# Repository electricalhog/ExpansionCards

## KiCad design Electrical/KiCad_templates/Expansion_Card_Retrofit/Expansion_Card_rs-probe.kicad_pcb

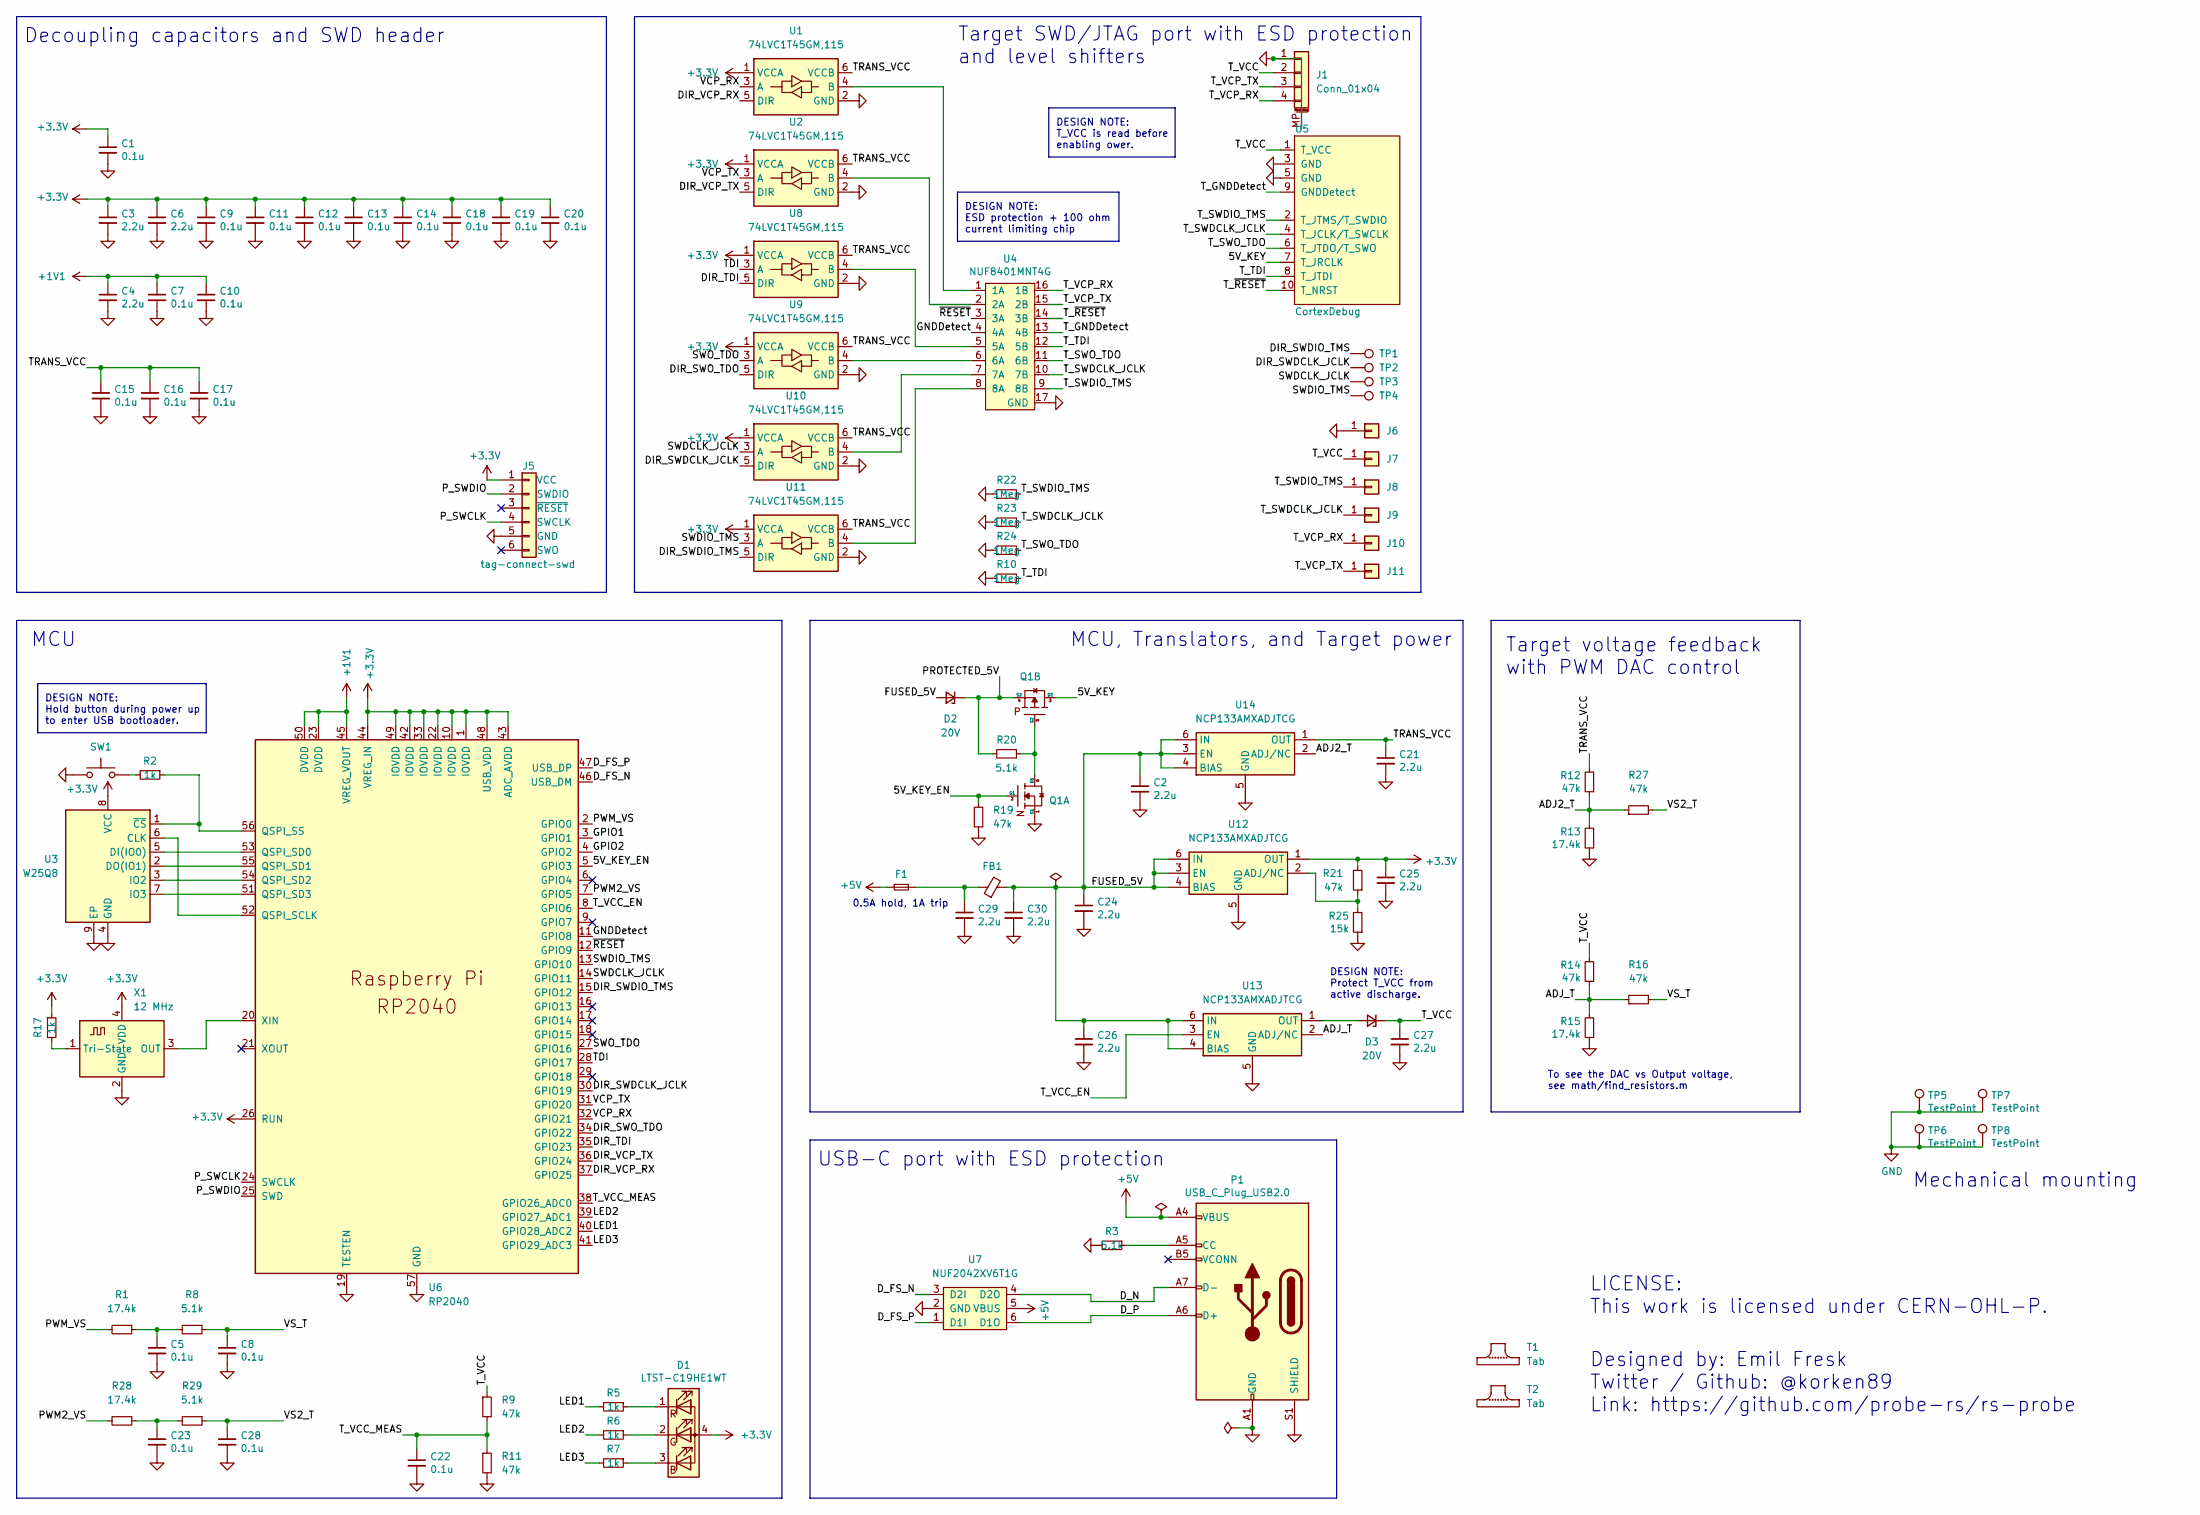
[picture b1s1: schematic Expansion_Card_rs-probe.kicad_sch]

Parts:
C1, C5, C7, C8, C9, C10, C11, C12, C13, C14, C15, C16, C17, C18, C19, C20, C22, C23, C28: 0.1u; C_0402; Tolerance 25V, X7R; LCSC C56392
C2, C3, C4, C6, C21, C24, C25, C26, C27, C29, C30: 2.2u; C_0402; Tolerance 10V, X5R; LCSC C77002
D1: LTST-C19HE1WT; LED_LiteOn_LTST-C19HE1WT; LCSC C427425, C458749
D2, D3: 20V; D_0402_1005Metric
F1: Fuse_Small; Fuse_0603_1608Metric; LCSC C210357
FB1: BLM15AX601SN1D; R_0402
J1: Conn_01x04; PinHeader_1x04_P1.00mm_Vertical_SMD_Pin1Left
J5: tag-connect-swd; Tag-Connect_TC2030-IDC-NL_2x03_P1.27mm_Vertical
J6, J7, J8, J9, J10, J11: Conn_01x01; pad_1.5x2.0mm
P1: USB_C_Plug_USB2.0; USB_C_Plug_Molex_105444
Q1: NTZD3155C or CMLDM3757-TR-PBFREE or DMC2400UV-7 o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; SOT-563; LCSC C895156, C236117, C3280275, C177025, C2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
R1, R13, R15, R28: 17.4k; R_0402; Tolerance 1%; LCSC C409673
R2, R5, R6, R7, R17: 1k; R_0402; Tolerance 1%; LCSC C106235
R3, R8, R29: 5.1k; R_0402; Tolerance 1%; LCSC C105872
R9, R11, R12, R14, R16, R19, R21, R27: 47k; R_0402; Tolerance 1%; LCSC C144757
R10, R22, R23, R24: 1Meg; R_0402; Tolerance 1%; LCSC C138033
R20: 5.1k; R_0402; Tolerance 1%
R25: 15k; R_0402; Tolerance 1%; LCSC C409673
SW1: B3U-1000P; SW_SPST_B3U-1000P; LCSC C79148, C713481
T1, T2: Tab
TP1, TP2, TP3, TP4: TestPoint; TestPoint_Pad_D1.0mm
TP5, TP6, TP7, TP8: TestPoint; TestPoint_Pad_1.5x1.5mm
U1, U2, U8, U9, U10, U11: 74LVC1T45GM,115; SOT-886; LCSC C548481, C548480, C548479
U3: W25Q8; USON-8-3x2mm-EP; LCSC C2063555, C2759920, C2983691, C559220, 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
U4: NUF8401MNT4G; DFN-16-1EP_1.6x4mm_P0.5mm; LCSC C895158
U5: CortexDebug; SHF-105-01-PCBEdge; LCSC C2935458, C150517, C920815
U6: RP2040; RP2040-QFN-56; LCSC C2040
U7: NUF2042XV6T1G; SOT-563; LCSC C90707
U12, U13, U14: NCP133AMXADJTCG; DFN-6-1EP_1.2x1.2mm_P0.4mm_EP0.3x0.94mm_PullBack; LCSC C457672
X1: 12 MHz; Crystal_SMD_2520-4Pin_2.5x2.0mm; LCSC C255991, C2681259, C3034288, C2901596

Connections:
+1V1: C4.1, C7.1, C10.1, U6.23 (DVDD), U6.45 (VREG_VOUT), U6.50 (DVDD)
+3.3V: C1.1, C3.1, C6.1, C9.1, C11.1, C12.1, C13.1, C14.1, C18.1, C19.1, C20.1, C25.1, D1.4 (A), J5.1 (VCC), R17.1, R21.2, U1.1 (VCCA), U2.1 (VCCA), U3.8 (VCC), U6.1 (IOVDD), U6.10 (IOVDD), U6.22 (IOVDD), U6.26 (RUN), U6.33 (IOVDD), U6.42 (IOVDD), U6.43 (ADC_AVDD), U6.44 (VREG_IN), U6.48 (USB_VDD), U6.49 (IOVDD), U8.1 (VCCA), U9.1 (VCCA), U10.1 (VCCA), U11.1 (VCCA), U12.1 (OUT), X1.4 (VDD)
+5V: F1.1, P1.A4 (VBUS), P1.A9 (VBUS), P1.B4 (VBUS), P1.B9 (VBUS), U7.5 (VBUS)
/5V_KEY: Q1.3 (D2), U5.7 (T_JRCLK)
/5V_KEY_EN: Q1.2 (G1), R19.2, U6.5 (GPIO3)
/ADJ2_T: R12.1, R13.2, R27.1, U14.2 (ADJ/NC)
/ADJ_T: R14.1, R15.2, R16.1, U13.2 (ADJ/NC)
/DIR_SWDCLK_JCLK: TP2.1, U6.30 (GPIO19), U10.5 (DIR)
/DIR_SWDIO_TMS: TP1.1, U6.15 (GPIO12), U11.5 (DIR)
/DIR_SWO_TDO: U6.34 (GPIO22), U9.5 (DIR)
/DIR_TDI: U6.35 (GPIO23), U8.5 (DIR)
/DIR_VCP_RX: U1.5 (DIR), U6.37 (GPIO25)
/DIR_VCP_TX: U2.5 (DIR), U6.36 (GPIO24)
/D_FS_N: U6.46 (USB_DM), U7.3 (D2I)
/D_FS_P: U6.47 (USB_DP), U7.1 (D1I)
/D_N: P1.A7 (D-), U7.4 (D2O)
/D_P: P1.A6 (D+), U7.6 (D1O)
/FUSED_5V: C2.1, C24.1, C26.1, C30.1, D2.2 (A), FB1.2, U12.3 (EN), U12.4 (BIAS), U12.6 (IN), U13.4 (BIAS), U13.6 (IN), U14.3 (EN), U14.4 (BIAS), U14.6 (IN)
/GNDDetect: U4.4 (4A), U6.11 (GPIO8)
/GPIO1: U6.3 (GPIO1)
/GPIO2: U6.4 (GPIO2)
/LED1: R5.2, U6.40 (GPIO28_ADC2)
/LED2: R6.2, U6.39 (GPIO27_ADC1)
/LED3: R7.2, U6.41 (GPIO29_ADC3)
/PROTECTED_5V: D2.1 (K), Q1.4 (S2), R20.2
/PWM2_VS: R28.2, U6.7 (GPIO5)
/PWM_VS: R1.2, U6.2 (GPIO0)
/P_SWCLK: J5.4 (SWCLK), U6.24 (SWCLK)
/P_SWDIO: J5.2 (SWDIO), U6.25 (SWD)
/SWDCLK_JCLK: TP3.1, U6.14 (GPIO11), U10.3 (A)
/SWDIO_TMS: TP4.1, U6.13 (GPIO10), U11.3 (A)
/SWO_TDO: U6.27 (GPIO16), U9.3 (A)
/TDI: U6.28 (GPIO17), U8.3 (A)
/TRANS_VCC: C15.1, C16.1, C17.1, C21.1, R12.2, U1.6 (VCCB), U2.6 (VCCB), U8.6 (VCCB), U9.6 (VCCB), U10.6 (VCCB), U11.6 (VCCB), U14.1 (OUT)
/T_GNDDetect: U4.13 (4B), U5.9 (GNDDetect)
/T_SWDCLK_JCLK: J9.1, R23.2, U4.10 (7B), U5.4 (T_JCLK/T_SWCLK)
/T_SWDIO_TMS: J8.1, R22.2, U4.9 (8B), U5.2 (T_JTMS/T_SWDIO)
/T_SWO_TDO: R24.2, U4.11 (6B), U5.6 (T_JTDO/T_SWO)
/T_TDI: R10.2, U4.12 (5B), U5.8 (T_JTDI)
/T_VCC: C27.1, D3.1 (K), J1.2, J7.1, R9.1, R14.2, U5.1 (T_VCC)
/T_VCC_EN: U6.8 (GPIO6), U13.3 (EN)
/T_VCC_MEAS: C22.1, R9.2, R11.1, U6.38 (GPIO26_ADC0)
/T_VCP_RX: J1.4, J10.1, U4.16 (1B)
/T_VCP_TX: J1.3, J11.1, U4.15 (2B)
/T_~RESET: U4.14 (3B), U5.10 (T_NRST)
/VCP_RX: U1.3 (A), U6.32 (GPIO21)
/VCP_TX: U2.3 (A), U6.31 (GPIO20)
/VS2_T: C28.1, R27.2, R29.1
/VS_T: C8.1, R8.1, R16.2
/~RESET: U4.3 (3A), U6.12 (GPIO9)
GND: C1.2, C2.2, C3.2, C4.2, C5.2, C6.2, C7.2, C8.2, C9.2, C10.2, C11.2, C12.2, C13.2, C14.2, C15.2, C16.2, C17.2, C18.2, C19.2, C20.2, C21.2, C22.2, C23.2, C24.2, C25.2, C26.2, C27.2, C28.2, C29.2, C30.2, J1.1, J1.MP (MountPin), J5.5 (GND), J6.1, P1.A1 (GND), P1.A12 (GND), P1.B1 (GND), P1.B12 (GND), P1.S1 (SHIELD), Q1.1 (S1), R3.2, R10.1, R11.2, R13.1, R15.1, R19.1, R22.1, R23.1, R24.1, R25.1, SW1.1, TP5.1, TP6.1, TP7.1, TP8.1, U1.2 (GND), U2.2 (GND), U3.4 (GND), U3.9 (EP), U4.17 (GND), U5.3 (GND), U5.5 (GND), U6.19 (TESTEN), U6.57 (GND), U7.2 (GND), U8.2 (GND), U9.2 (GND), U10.2 (GND), U11.2 (GND), U12.5 (GND), U12.7 (GND), U13.5 (GND), U13.7 (GND), U14.5 (GND), U14.7 (GND), X1.2 (GND)
unnamed: C5.1, R1.1, R8.2
unnamed: C23.1, R28.1, R29.2
unnamed: C29.1, F1.2, FB1.1
unnamed: D1.3 (BK), R7.1
unnamed: D1.2 (GK), R6.1
unnamed: D1.1 (RK), R5.1
unnamed: D3.2 (A), U13.1 (OUT)
unnamed: P1.A5 (CC), R3.1
unnamed: Q1.5 (G2), Q1.6 (D1), R20.1
unnamed: R2.2, SW1.2
unnamed: U1.4 (B), U4.1 (1A)
unnamed: U2.4 (B), U4.2 (2A)
unnamed: U3.6 (CLK), U6.52 (QSPI_SCLK)
unnamed: U3.5 (DI(IO0)), U6.53 (QSPI_SD0)
unnamed: U3.2 (DO(IO1)), U6.55 (QSPI_SD1)
unnamed: U3.3 (IO2), U6.54 (QSPI_SD2)
unnamed: U3.7 (IO3), U6.51 (QSPI_SD3)
unnamed: R2.1, U3.1 (~CS), U6.56 (QSPI_SS)
unnamed: U4.5 (5A), U8.4 (B)
unnamed: U4.6 (6A), U9.4 (B)
unnamed: U6.20 (XIN), X1.3 (OUT)
unnamed: U4.7 (7A), U10.4 (B)
unnamed: U4.8 (8A), U11.4 (B)
unnamed: R21.1, R25.2, U12.2 (ADJ/NC)
unnamed: R17.2, X1.1 (Tri-State)

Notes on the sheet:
Target voltage feedback with PWM DAC control
DESIGN NOTE: ESD protection + 100 ohm current limiting chip
DESIGN NOTE: Protect T_VCC from active discharge.
Designed by: Emil Fresk Twitter / Github: @korken89 Link: https://github.com/probe-rs/rs-probe
DESIGN NOTE: T_VCC is read before enabling ower.
Mechanical mounting
DESIGN NOTE: Hold button during power up to enter USB bootloader.
0.5A hold, 1A trip
MCU, Translators, and Target power
MCU
USB-C port with ESD protection
To see the DAC vs Output voltage, see math/find_resistors.m
Target SWD/JTAG port with ESD protection and level shifters
Decoupling capacitors and SWD header
LICENSE: This work is licensed under CERN-OHL-P.

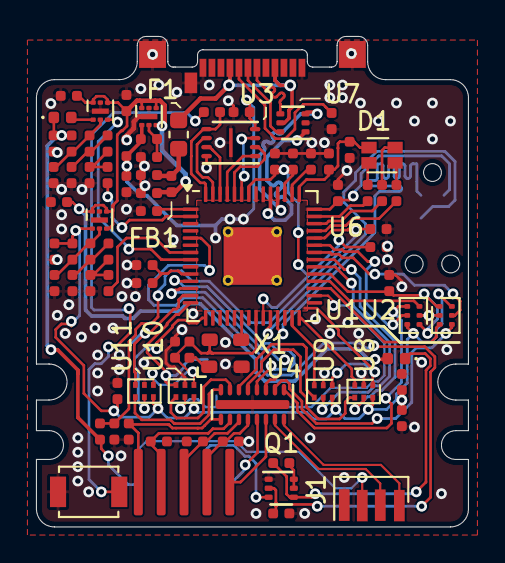
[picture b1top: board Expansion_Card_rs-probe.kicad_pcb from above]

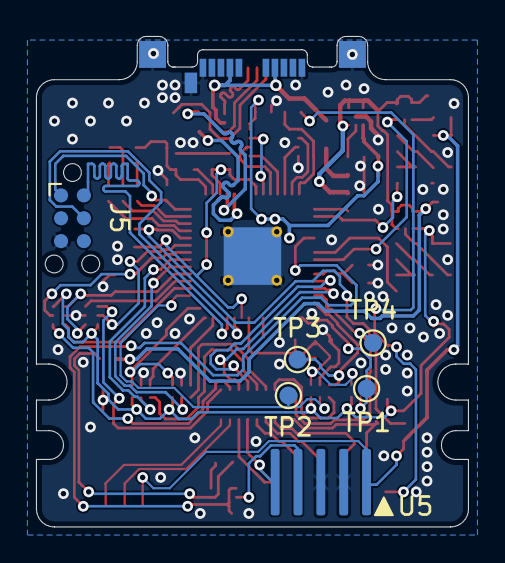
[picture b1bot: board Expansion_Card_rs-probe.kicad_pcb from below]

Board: 2 copper layers, 24.0 x 27.3 mm, 91 parts (8 on the bottom side), 74 nets.

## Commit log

2024-07-15 airwires solved
2024-07-15 silkscreen and DRC progress
2025-02-18 images and models
2025-03-19 VCP and 3d models
2025-06-01 v0 ordered
2025-06-01 small change

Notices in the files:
Electrical/KiCad_templates/Expansion_Card_Retrofit/Expansion_Card_rs-probe.kicad_pcb:
This work is licensed under a Creative Commons Attribution 4.0 International License
